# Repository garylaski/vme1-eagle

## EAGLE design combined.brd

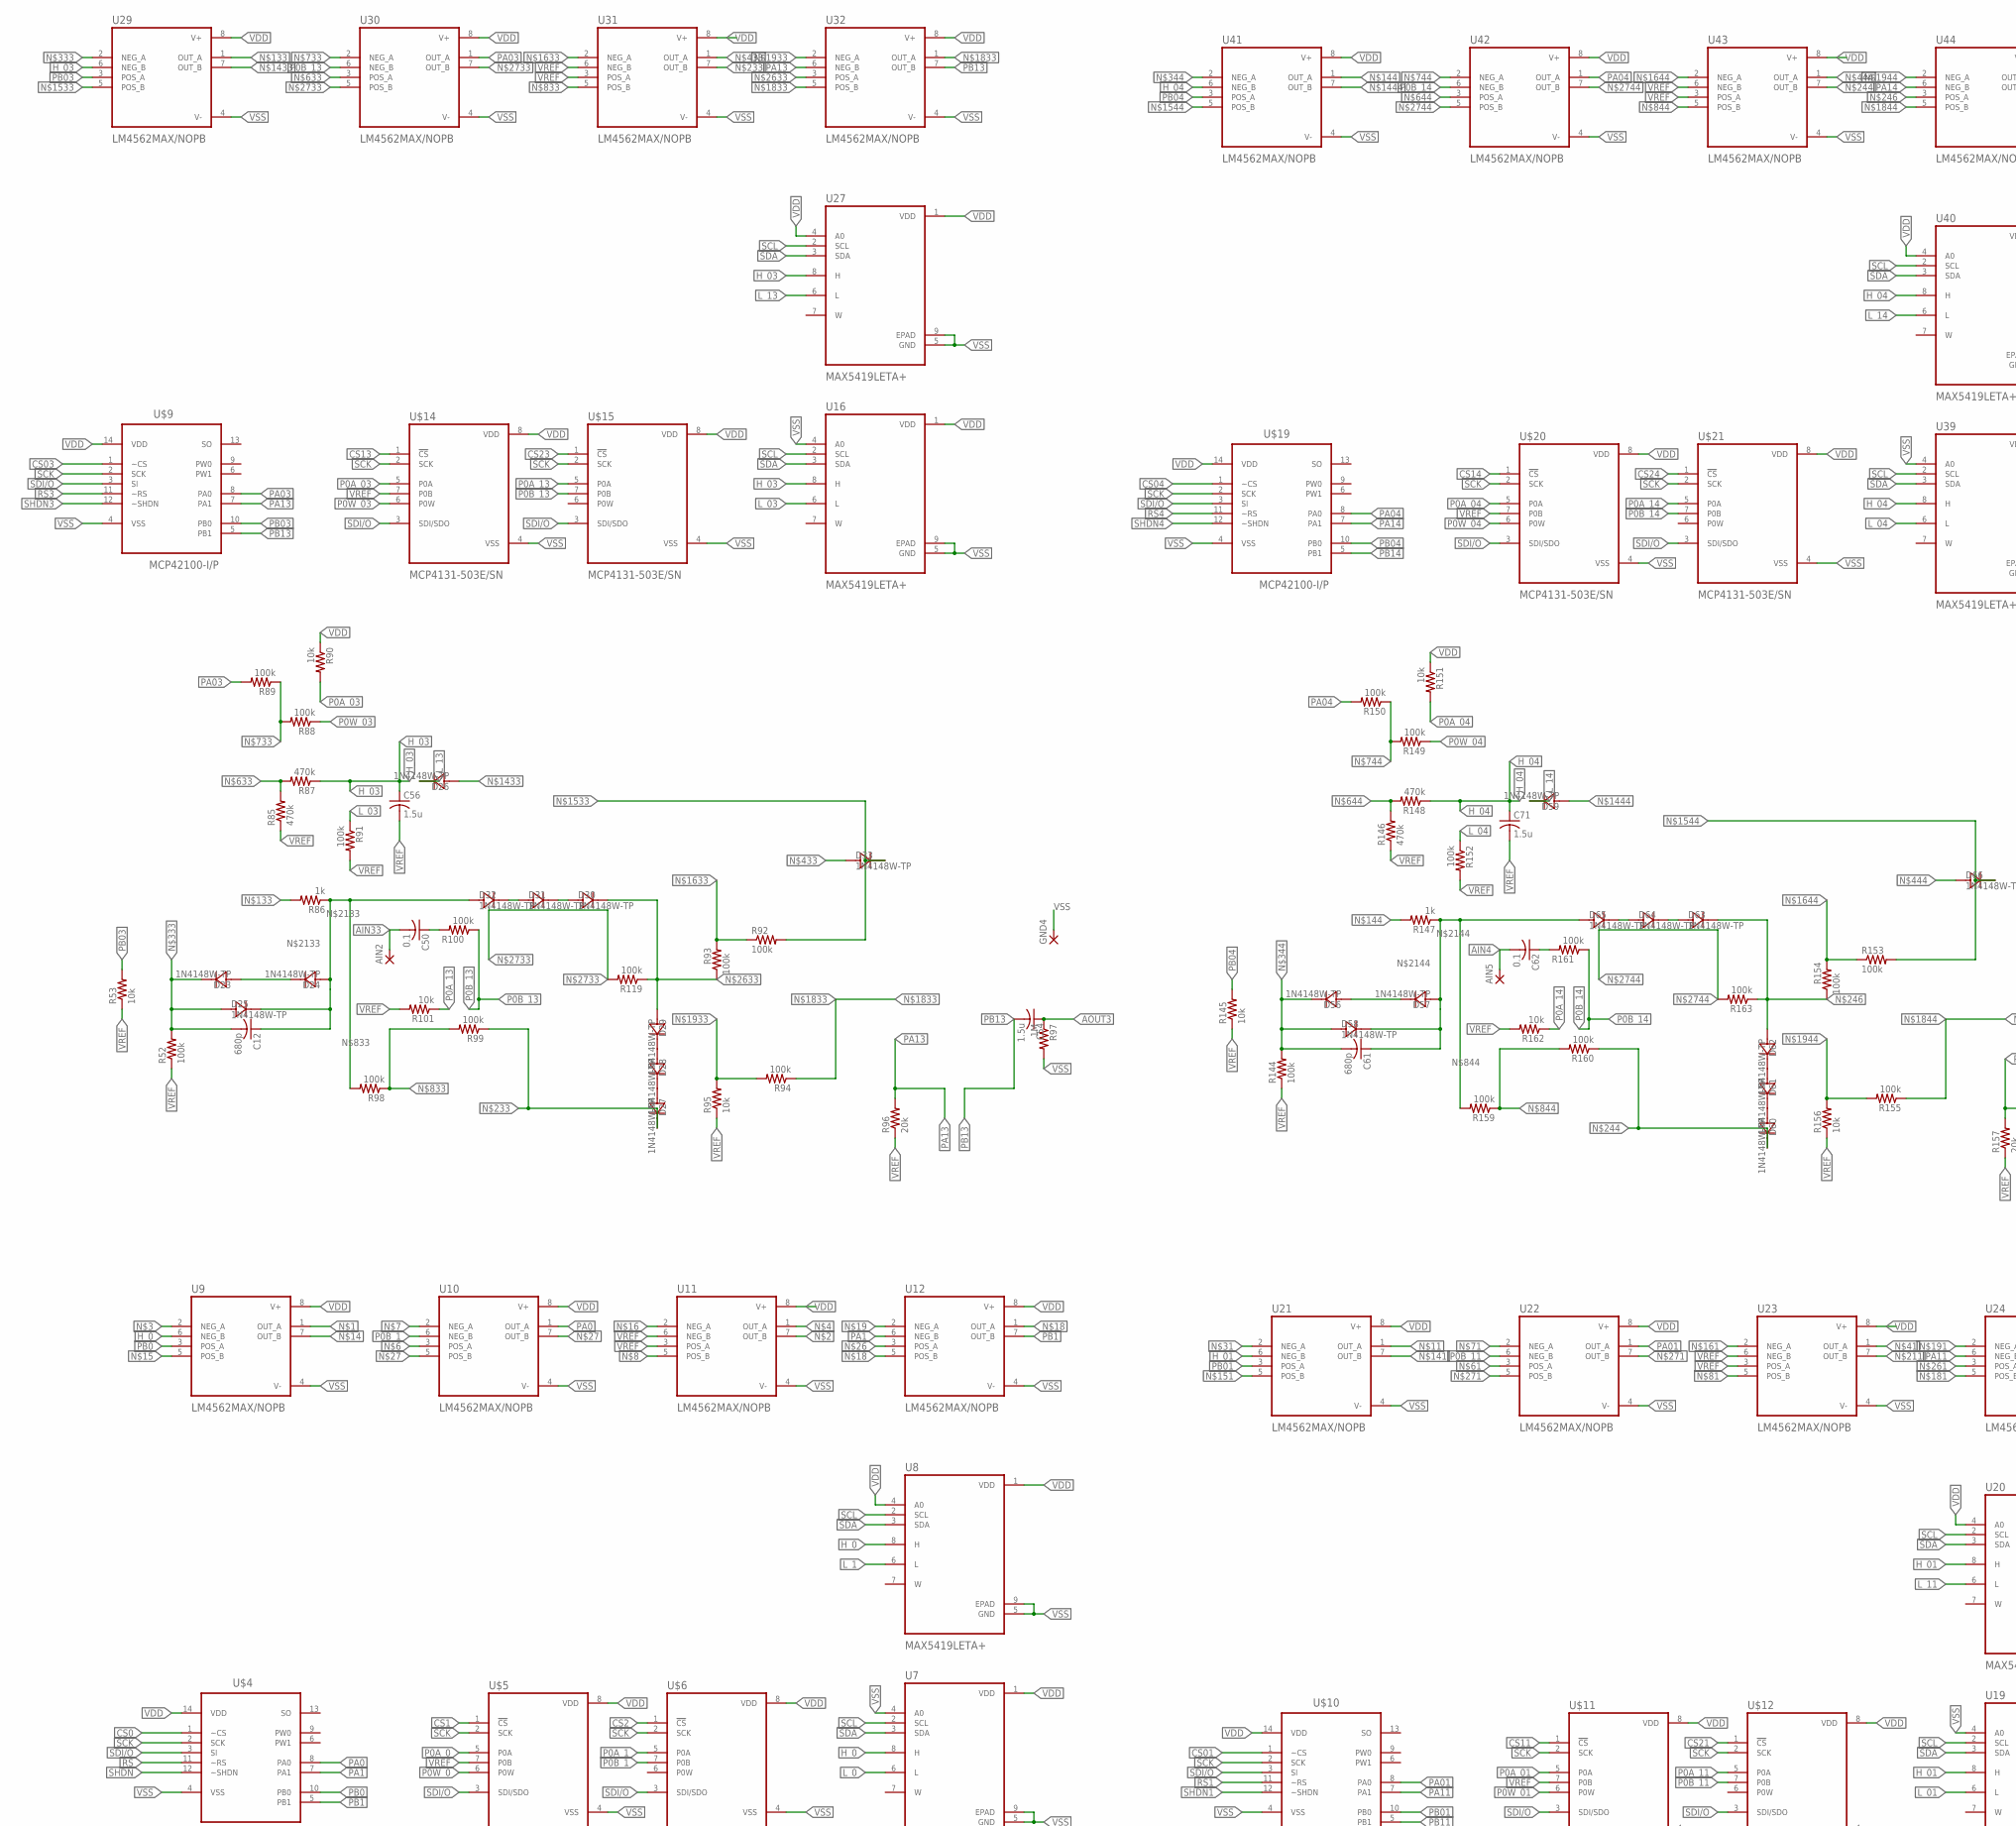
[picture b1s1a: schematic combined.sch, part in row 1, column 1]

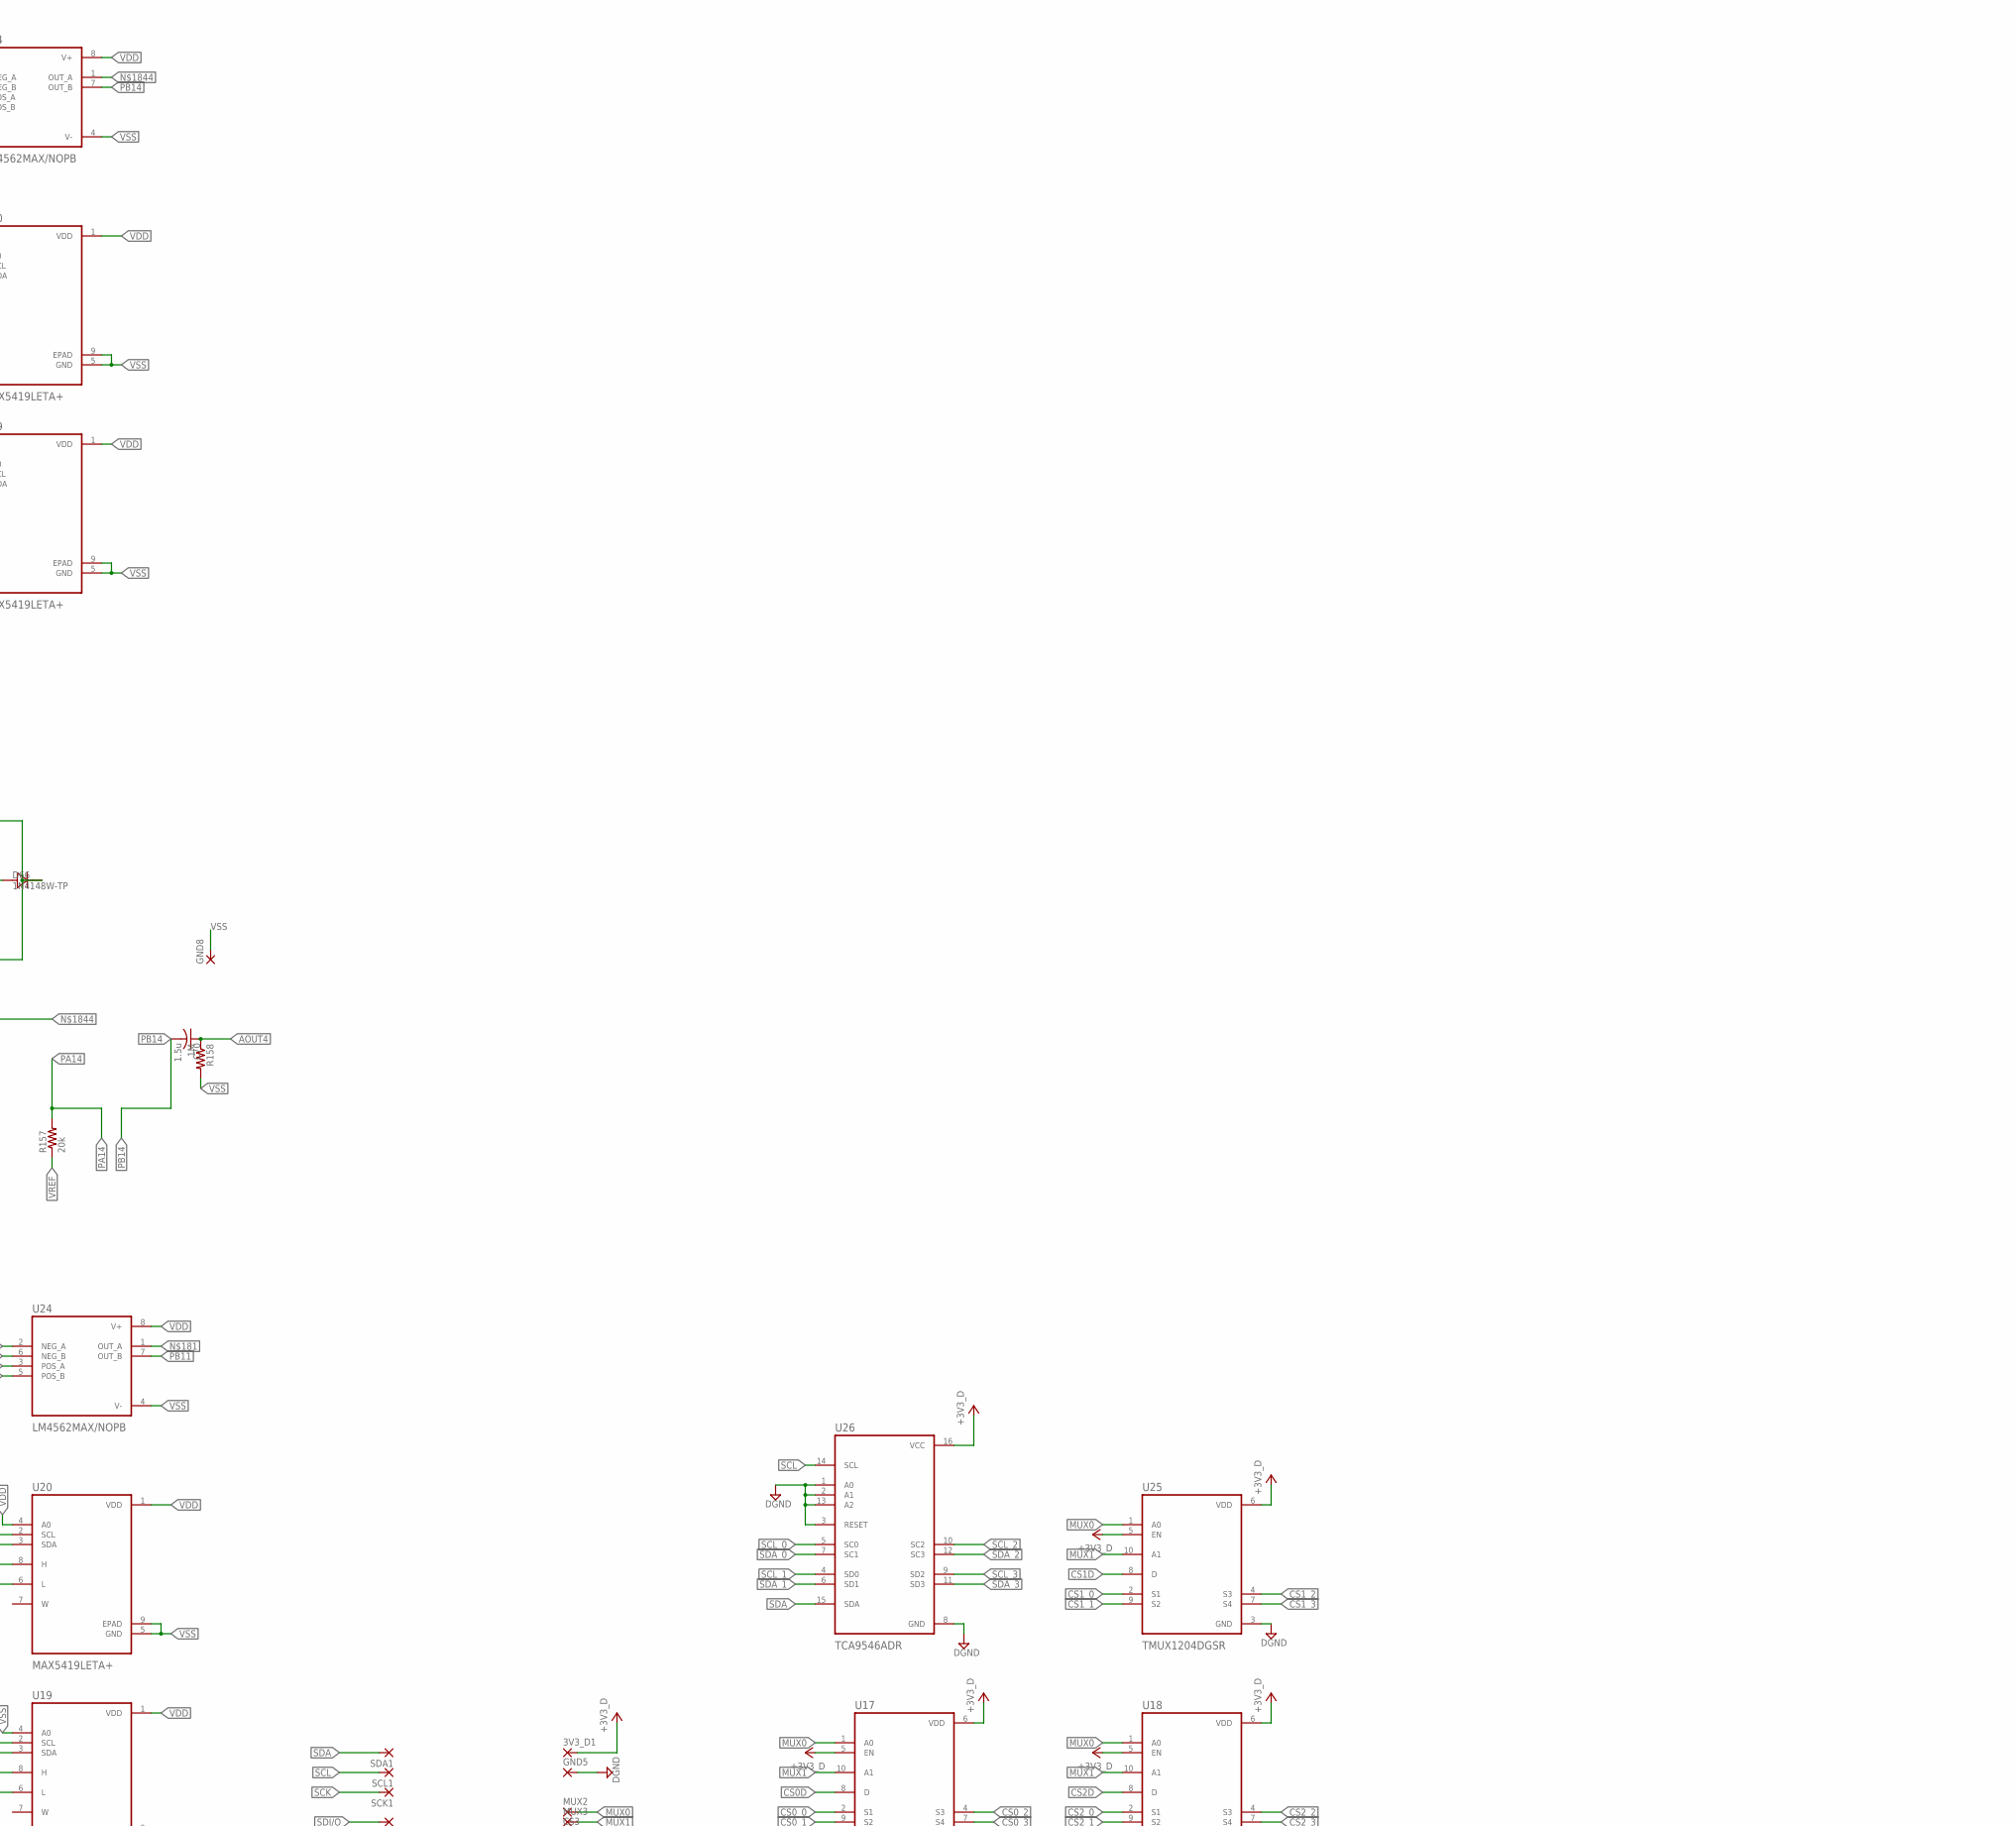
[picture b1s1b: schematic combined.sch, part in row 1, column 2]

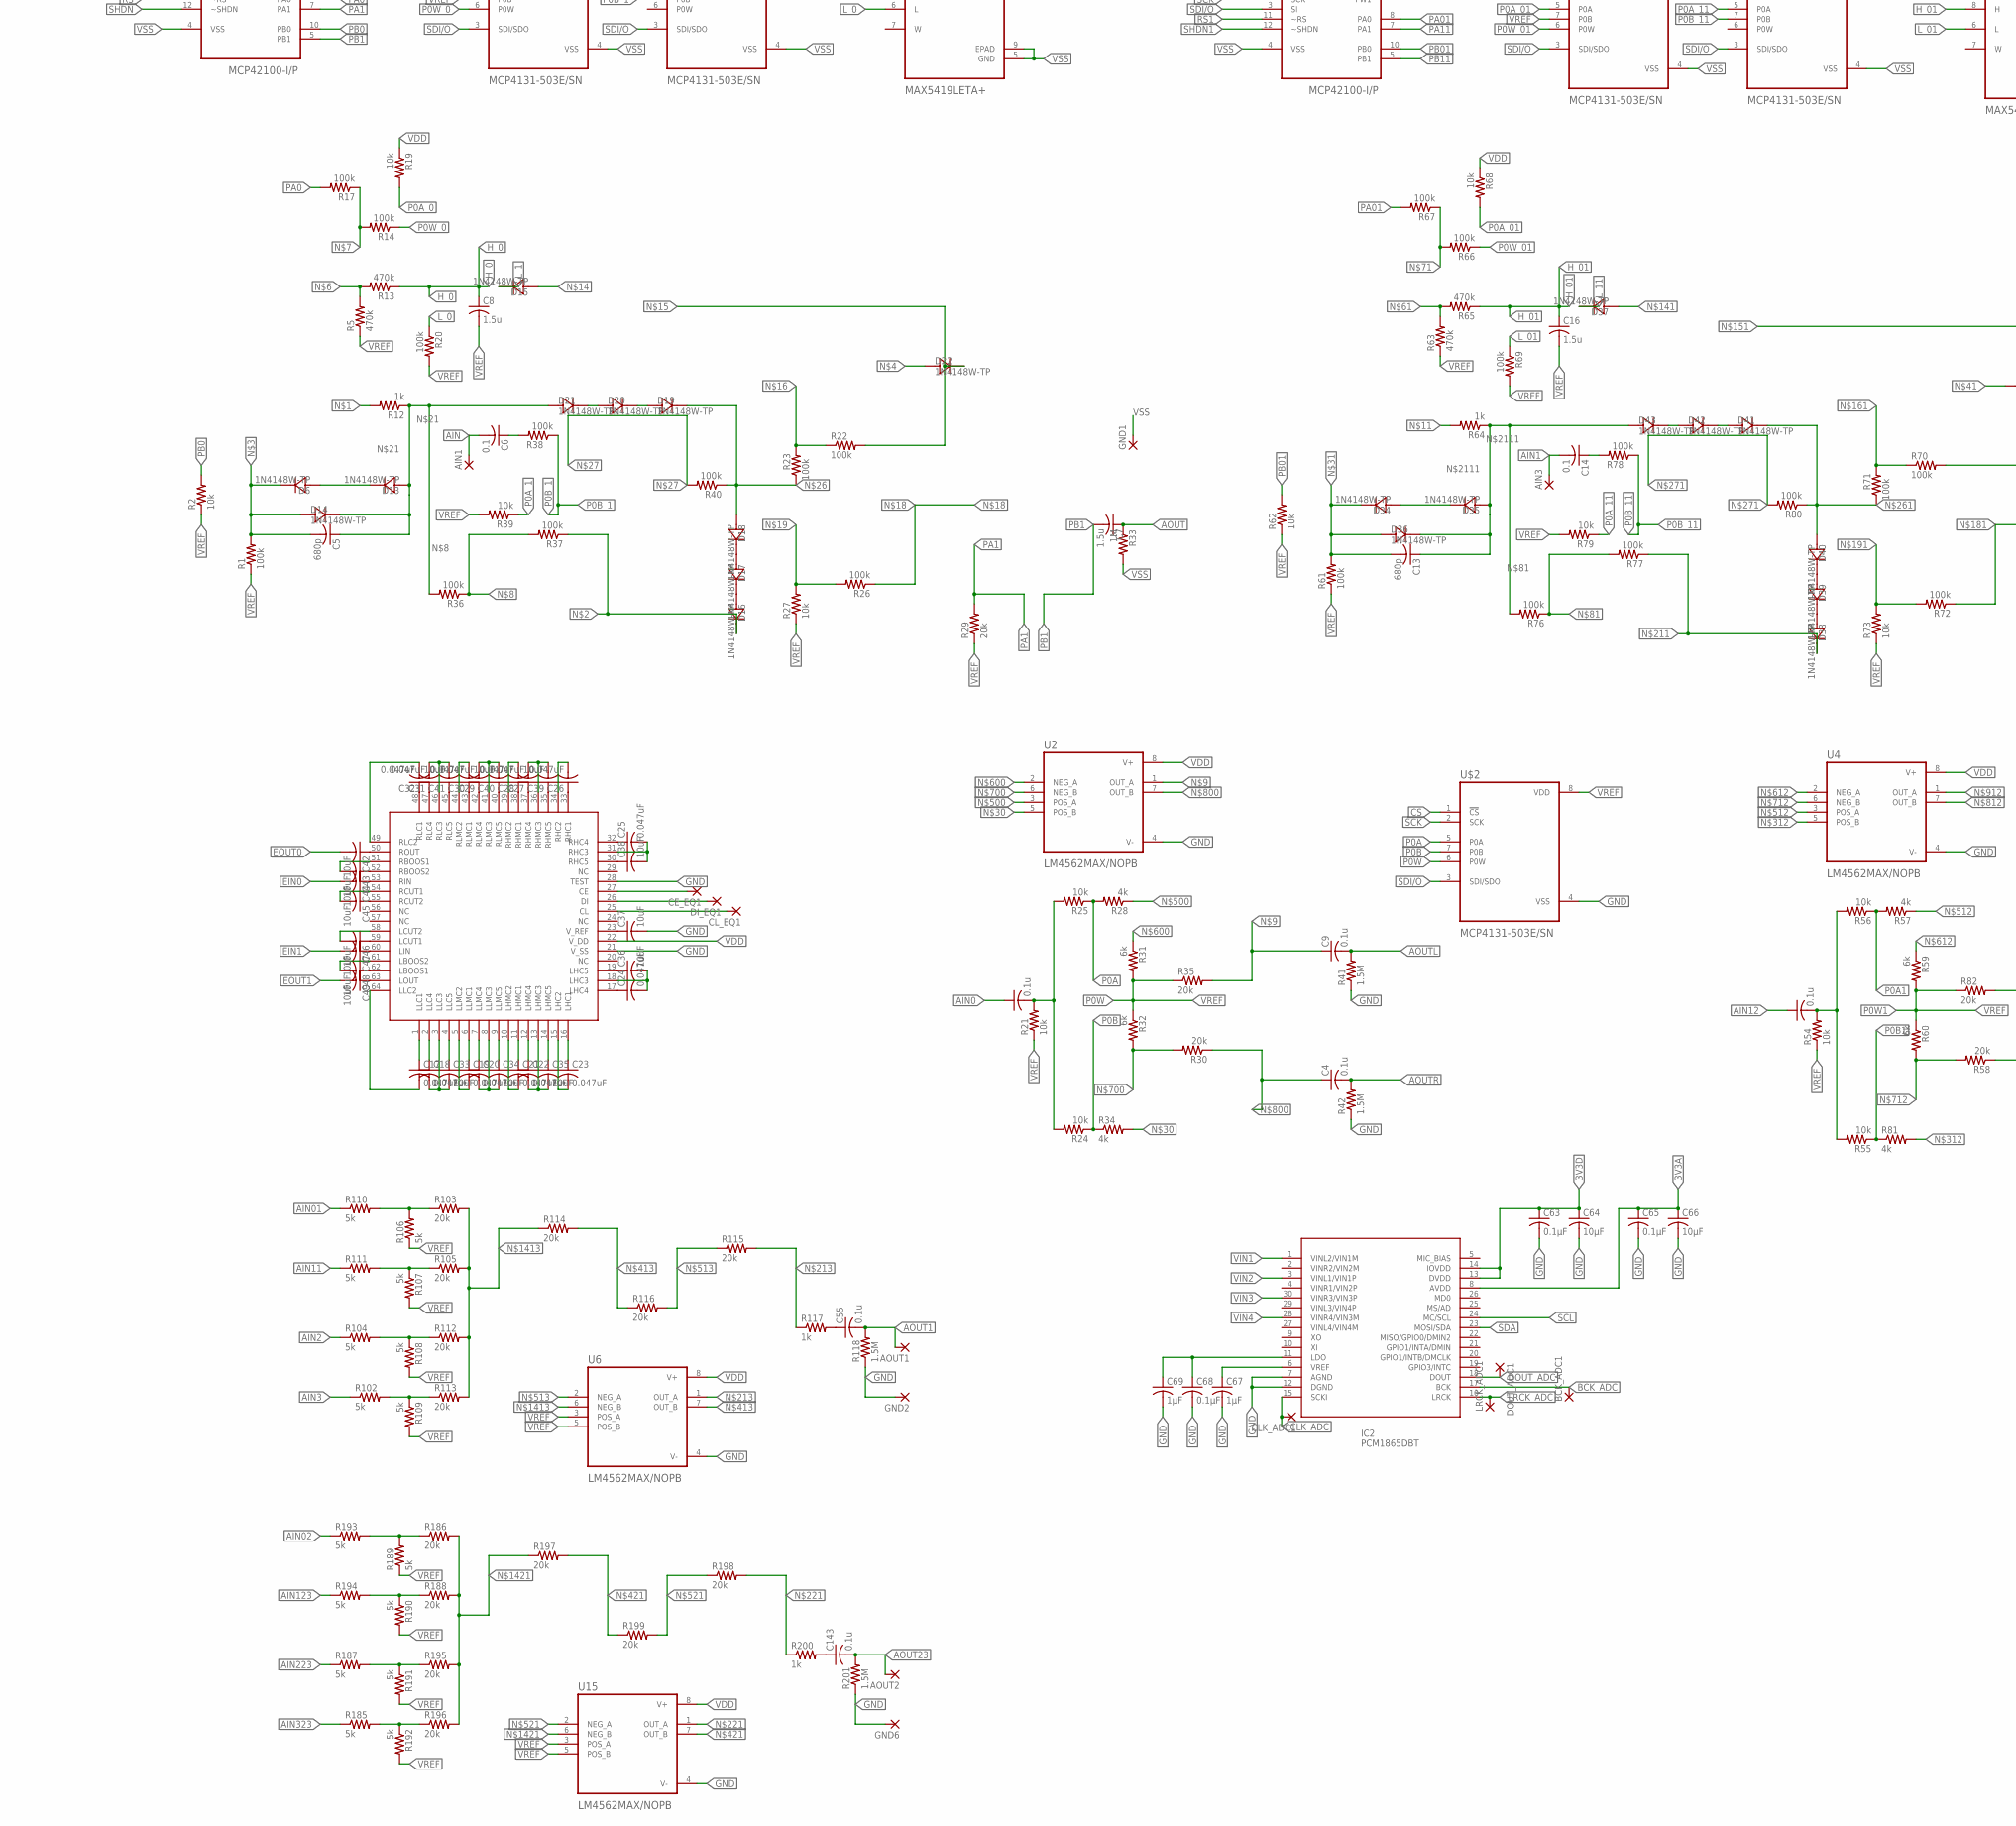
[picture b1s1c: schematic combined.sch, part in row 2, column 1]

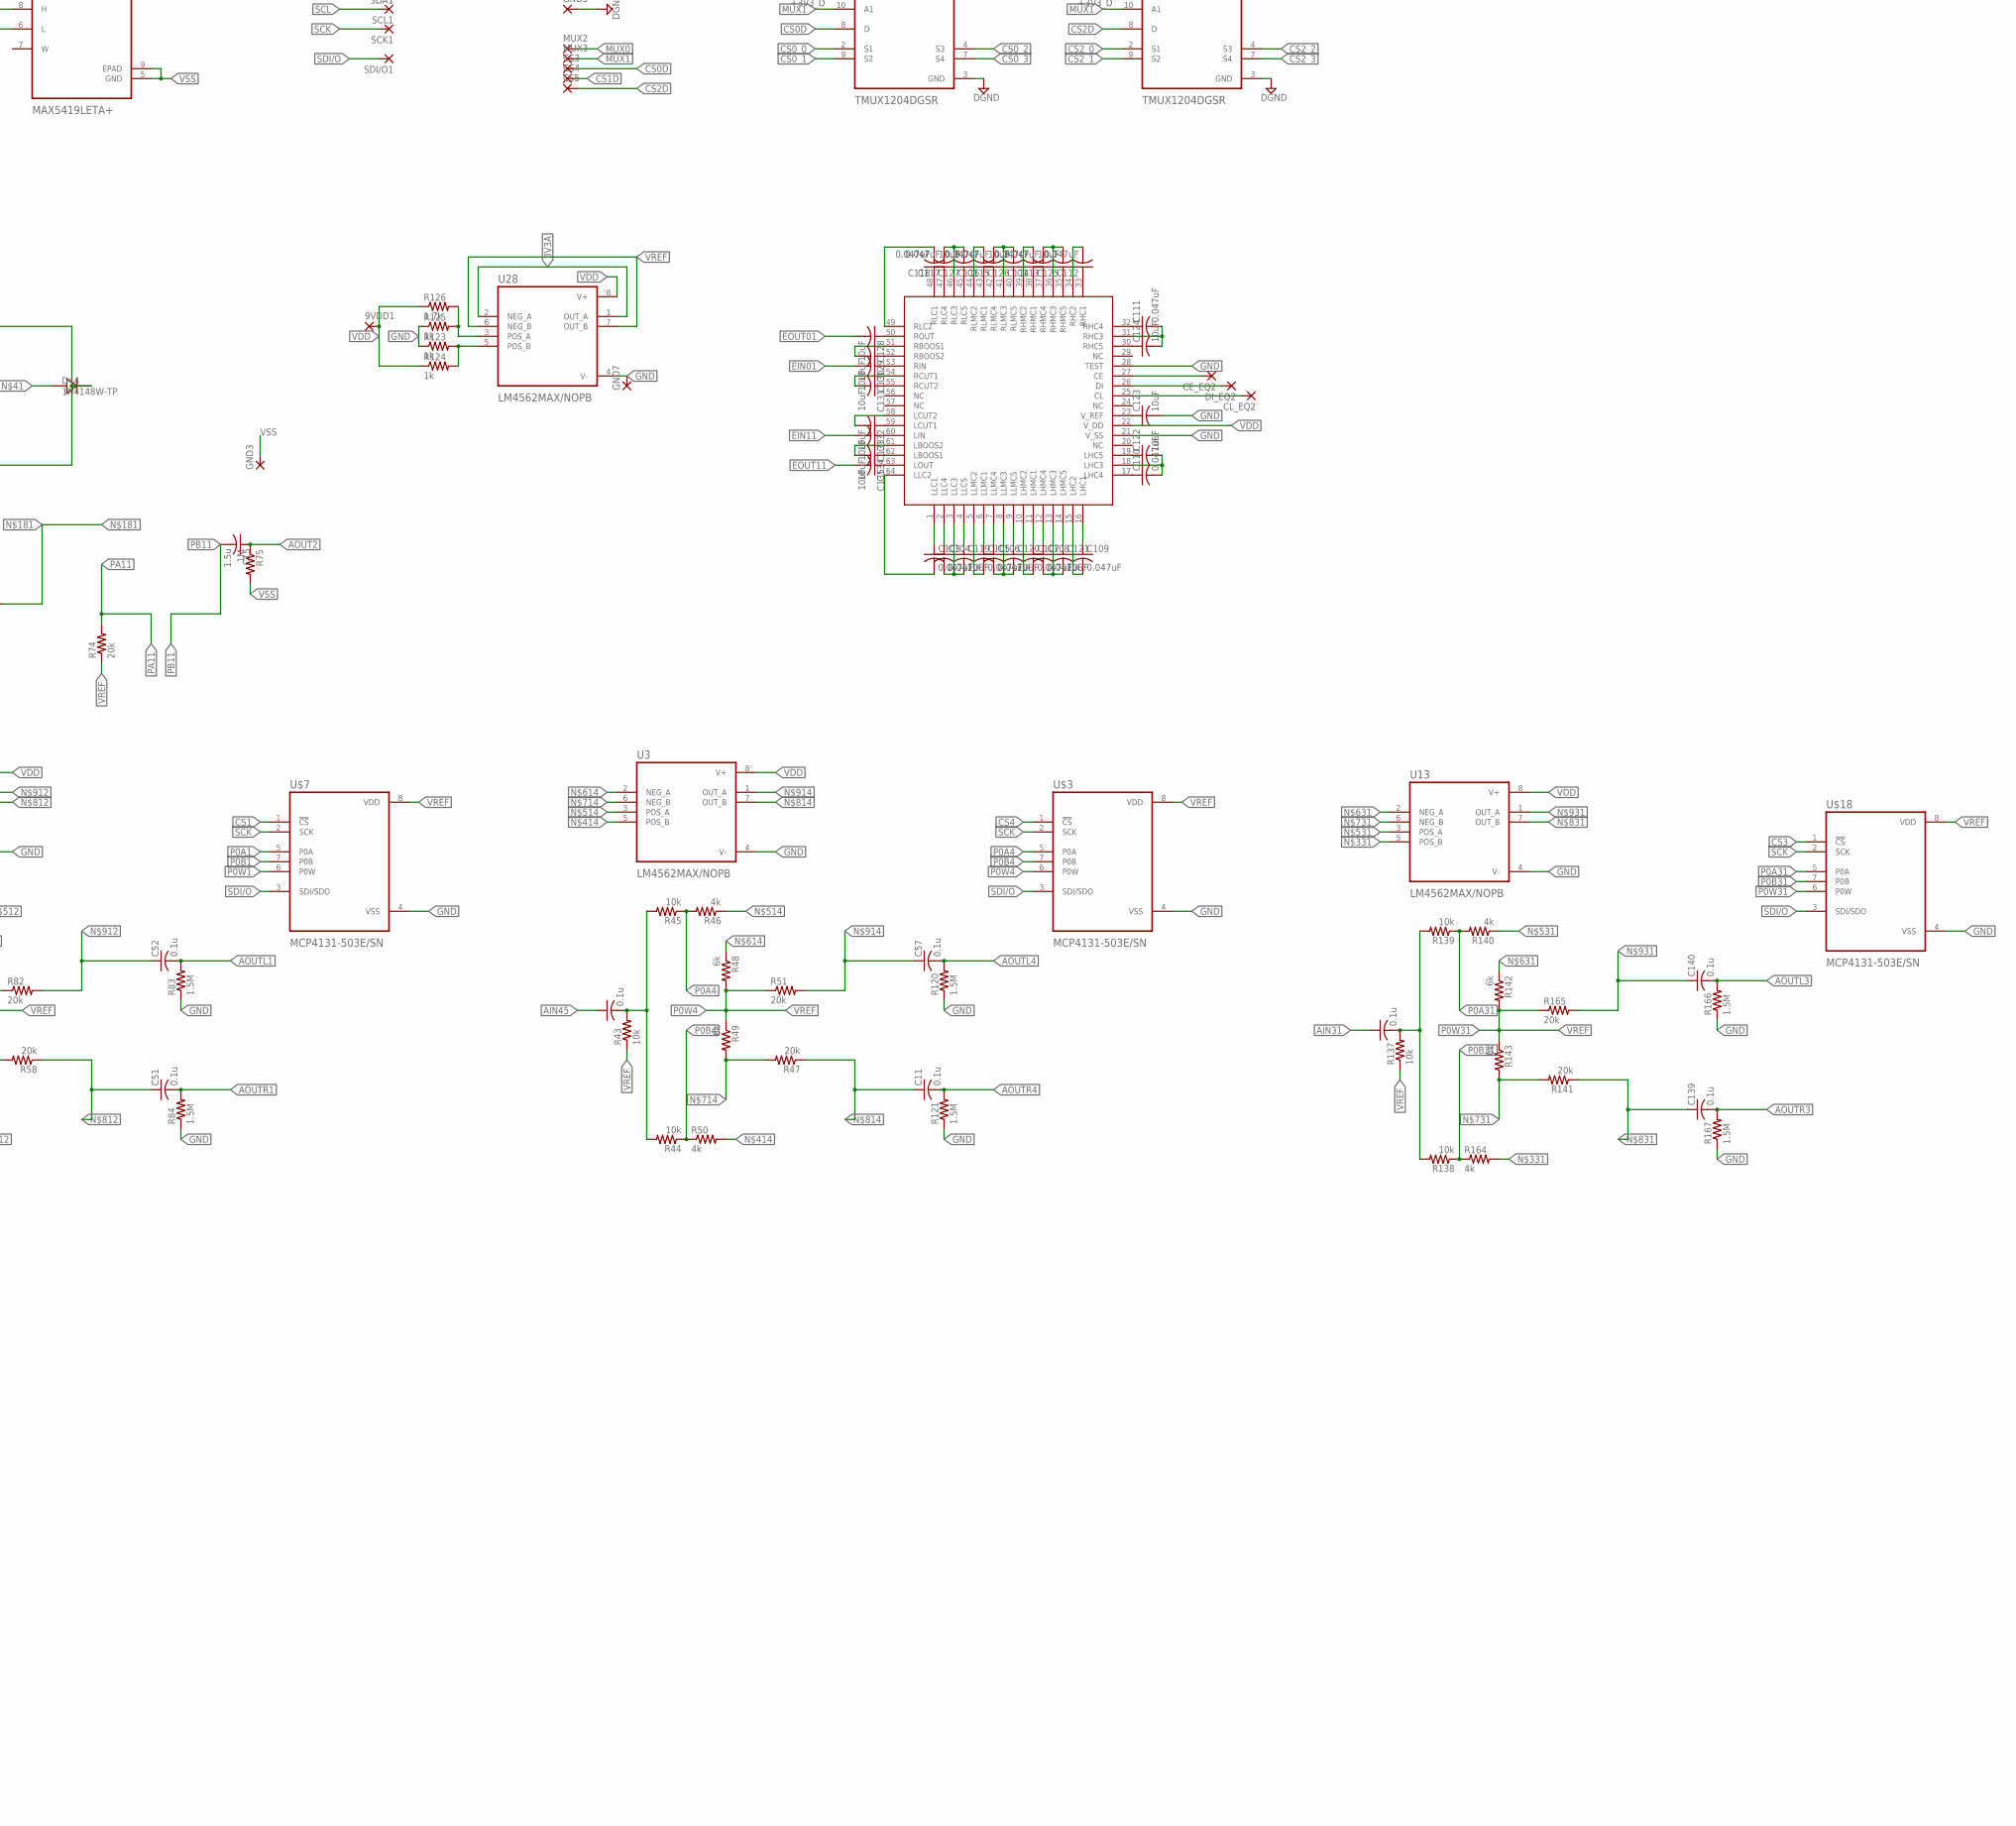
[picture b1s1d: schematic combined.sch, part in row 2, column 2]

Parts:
3V3_D1, 9VDD1: SMD2; SMD1,27-2,54
AIN1, AIN2, AIN3, AIN5: SMD5; SMD2,54-5,08
AOUT1, AOUT2: SMD5; SMD2,54-5,08
BCK_ADC1: SMD2; SMD1,27-2,54
C4, C9, C10, C11, C51, C52, C53, C55, C57, C58, C139, C140, C141, C143: 0.1u; C0402
C5, C12, C13, C61: 680p; C0402
C6, C14, C50, C62: 0.1; C0402
C7, C8, C15, C16, C54, C56, C70, C71: 1.5u; C0402
C17, C18, C19, C20, C21, C22, C23, C24, C25, C26, C27, C28, C29, C30, C31, C32, C103, C104, C105, C106, C107, C108, C109, C110, C111, C112, C113, C114, C115, C116, C117, C118: 0.047uF; C0402
C33, C34, C35, C36, C37, C38, C39, C40, C41, C42, C43, C44, C45, C46, C47, C48, C49, C119, C120, C121, C122, C123, C124, C125, C126, C127, C128, C129, C130, C131, C132, C133, C134, C135: 10uF; C0402
C63, C65, C68: 0.1μF; C0402
C64, C66: 10μF; C0402
C67, C69: 1μF; C0402
CE_EQ1, CE_EQ2: SMD2; SMD1,27-2,54
CLK_ADC1: SMD2; SMD1,27-2,54
CL_EQ1, CL_EQ2: SMD2; SMD1,27-2,54
CS3, CS4, CS5: SMD2; SMD1,27-2,54
D6, D13, D14, D15, D16, D17, D18, D19, D20, D21, D22, D23, D24, D25, D26, D27, D28, D29, D30, D31, D32, D33, D34, D35, D36, D37, D38, D39, D40, D41, D42, D43, D44, D56, D57, D58, D59, D60, D61, D62, D63, D64, D65, D66: 1N4148W-TP; SOD123
DI_EQ1, DI_EQ2: SMD2; SMD1,27-2,54
DOUT_ADC1: SMD2; SMD1,27-2,54
GND1, GND2, GND3, GND4, GND6, GND8: SMD5; SMD2,54-5,08
GND5, GND7: SMD2; SMD1,27-2,54
IC2: PCM1865DBT; TSSOP-30
LRCK_ADC1: SMD2; SMD1,27-2,54
MUX2, MUX3: SMD2; SMD1,27-2,54
R1, R14, R17, R20, R22, R23, R26, R36, R37, R38, R40, R52, R61, R66, R67, R69, R70, R71, R72, R76, R77, R78, R80, R88, R89, R91, R92, R93, R94, R98, R99, R100, R119, R144, R149, R150, R152, R153, R154, R155, R159, R160, R161, R163: 100k; R0402
R2, R19, R21, R24, R25, R27, R39, R43, R44, R45, R53, R54, R55, R56, R62, R68, R73, R79, R90, R95, R101, R137, R138, R139, R145, R151, R156, R162: 10k; R0402
R5, R13, R63, R65, R85, R87, R146, R148: 470k; R0402
R12, R64, R86, R117, R123, R124, R125, R147, R200: 1k; R0402
R28, R34, R46, R50, R57, R81, R140, R164: 4k; R0402
R29, R30, R35, R47, R51, R58, R74, R82, R96, R103, R105, R112, R113, R114, R115, R116, R141, R157, R165, R186, R188, R195, R196, R197, R198, R199: 20k; R0402
R31, R32, R48, R49, R59, R60, R142, R143: 6k; R0402
R33, R75, R97, R158: 1M; R0402
R41, R42, R83, R84, R118, R120, R121, R166, R167, R201: 1.5M; R0402
R102, R104, R106, R107, R108, R109, R110, R111, R185, R187, R189, R190, R191, R192, R193, R194: 5k; R0402
R126: 1.7k; R0402
SCK1: SMD2; SMD1,27-2,54
SCL1: SMD2; SMD1,27-2,54
SDA1: SMD2; SMD1,27-2,54
SDI/O1: SMD2; SMD1,27-2,54
U2, U3, U4, U6, U9, U10, U11, U12, U13, U15, U21, U22, U23, U24, U28, U29, U30, U31, U32, U41, U42, U43, U44: LM4562MAX/NOPB; SOIC127P599X175-8N
U7, U8, U16, U19, U20, U27, U39, U40: MAX5419LETA+; SON65P300X300X80-9N
U17, U18, U25: TMUX1204DGSR; SOP50P490X110-10N
U26: TCA9546ADR; SOIC127P600X175-16N
U$2, U$3, U$5, U$6, U$7, U$11, U$12, U$14, U$15, U$18, U$20, U$21: MCP4131-503E/SN; SOIC127P599X175-8N
U$4, U$9, U$10, U$19: MCP42100-I/P; DIP254P762X432-14
U$13, U$16: LC75281E; QFP80P1720X1720X270-64N

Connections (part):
3V3A: C65.1, C66.1, IC2.8 (AVDD), U28.1 (OUT_A), U28.2 (NEG_A)
3V3D: C63.1, C64.1, IC2.13 (DVDD), IC2.14 (IOVDD)
+3V3: 3V3_D1.1, U17.5 (EN), U17.6 (VDD), U18.5 (EN), U18.6 (VDD), U25.5 (EN), U25.6 (VDD), U26.16 (VCC)
AIN: AIN1.1, C6.2
AIN0: C10.1
AIN1: AIN3.1, C14.2
AIN01: R110.1
AIN2: R104.1
AIN02: R193.1
AIN3: R102.1
AIN4: AIN5.1, C62.2
AIN11: R111.1
AIN12: C53.1
AIN31: C141.1
AIN33: AIN2.1, C50.2
AIN45: C58.1
AIN123: R194.1
AIN223: R187.1
AIN323: R185.1
AOUT: C7.1, R33.1
AOUT1: AOUT1.1, C55.2, R118.2
AOUT2: C15.1, R75.1
AOUT3: C54.1, R97.1
AOUT4: C70.1, R158.1
AOUT23: AOUT2.1, C143.2, R201.2
AOUTL: C9.2, R41.2
AOUTL1: C52.2, R83.2
AOUTL3: C140.2, R166.2
AOUTL4: C57.2, R120.2
AOUTR: C4.2, R42.2
AOUTR1: C51.2, R84.2
AOUTR3: C139.2, R167.2
AOUTR4: C11.2, R121.2
BCK_ADC: BCK_ADC1.1, IC2.17 (BCK)
CLK_ADC: CLK_ADC1.1, IC2.15 (SCKI)
CS: U$2.1 (!CS)
CS0: U$4.1 (~CS)
CS0D: CS3.1, U17.8 (D)
CS0_0: U17.2 (S1)
CS0_1: U17.9 (S2)
CS0_2: U17.4 (S3)
CS0_3: U17.7 (S4)
CS1: U$5.1 (!CS), U$7.1 (!CS)
CS01: U$10.1 (~CS)
CS1D: CS4.1, U25.8 (D)
CS1_0: U25.2 (S1)
CS1_1: U25.9 (S2)
CS1_2: U25.4 (S3)
CS1_3: U25.7 (S4)
CS2: U$6.1 (!CS)
CS2D: CS5.1, U18.8 (D)
CS2_0: U18.2 (S1)
CS2_1: U18.9 (S2)
CS2_2: U18.4 (S3)
CS2_3: U18.7 (S4)
CS03: U$9.1 (~CS)
CS3: U$18.1 (!CS)
CS04: U$19.1 (~CS)
CS4: U$3.1 (!CS)
CS11: U$11.1 (!CS)
CS13: U$14.1 (!CS)
CS14: U$20.1 (!CS)
CS21: U$12.1 (!CS)
CS23: U$15.1 (!CS)
CS24: U$21.1 (!CS)
DGND: GND5.1, U17.3 (GND), U18.3 (GND), U25.3 (GND), U26.1 (A0), U26.2 (A1), U26.3 (RESET), U26.8 (GND), U26.13 (A2)
DOUT_ADC: DOUT_ADC1.1, IC2.18 (DOUT)
EIN0: C44.2
EIN1: C47.2
EIN01: C130.2
EIN11: C133.2
EOUT0: C42.2
EOUT1: C49.2
EOUT01: C128.2
EOUT11: C135.2
EQ1_CE1: CE_EQ1.1, U$13.27 (CE)
EQ1_CE2: CE_EQ2.1, U$16.27 (CE)
EQ1_CL1: CL_EQ1.1, U$13.25 (CL)
EQ1_CL2: CL_EQ2.1, U$16.25 (CL)
EQ1_DI1: DI_EQ1.1, U$13.26 (DI)
EQ1_DI2: DI_EQ2.1, U$16.26 (DI)
GND: C37.2, C63.2, C64.2, C65.2, C66.2, C67.2, C68.2, C69.2, C123.2, GND2.1, GND6.1, GND7.1, IC2.7 (AGND), IC2.12 (DGND), R41.1, R42.1, R83.1, R84.1, R118.1, R120.1, R121.1, R123.1, R125.1, R166.1, R167.1, R201.1, U2.4 (V-), U3.4 (V-), U4.4 (V-), U6.4 (V-), U13.4 (V-), U15.4 (V-), U28.4 (V-), U$2.4 (VSS), U$3.4 (VSS), U$7.4 (VSS), U$13.21 (V_SS), U$13.28 (TEST), U$16.21 (V_SS), U$16.28 (TEST), U$18.4 (VSS)
H_0: C8.1, R13.1, U7.8 (H), U8.8 (H), U9.6 (NEG_B)
H_01: C16.1, R65.1, U19.8 (H), U20.8 (H), U21.6 (NEG_B)
H_03: C56.1, R87.1, U16.8 (H), U27.8 (H), U29.6 (NEG_B)
H_04: C71.1, R148.1, U39.8 (H), U40.8 (H), U41.6 (NEG_B)
LRCK_ADC: IC2.16 (LRCK), LRCK_ADC1.1
L_0: R20.1, U7.6 (L)
L_1: D15.C, U8.6 (L)
L_01: R69.1, U19.6 (L)
L_03: R91.1, U16.6 (L)
L_04: R152.1, U39.6 (L)
L_11: D37.C, U20.6 (L)
L_13: D26.C, U27.6 (L)
L_14: D59.C, U40.6 (L)
MUX0: MUX2.1, U17.1 (A0), U18.1 (A0), U25.1 (A0)
MUX1: MUX3.1, U17.10 (A1), U18.10 (A1), U25.10 (A1)
unnamed: D6.A, D13.C, R12.2, U9.1 (OUT_A)
unnamed: D16.C, D17.A, D18.C, R37.1, U11.7 (OUT_B)
unnamed: C5.2, D6.C, D14.A, D16.A, D17.C, R1.2, U9.2 (NEG_A)
unnamed: C6.1, D22.A, R38.2, U11.1 (OUT_A)
unnamed: D20.A, D21.C
unnamed: D19.A, D20.C, R5.2, R13.2, U10.3 (POS_A)
unnamed: R14.2, R17.1, U10.2 (NEG_A)
unnamed: R36.1, R37.2, U11.5 (POS_B)
unnamed: C9.1, R35.2, U2.1 (OUT_A)
unnamed: C10.2, R21.2, R24.2, R25.2
unnamed: R64.2, U21.1 (OUT_A)
unnamed: D34.A, D35.C
unnamed: D15.A, U9.7 (OUT_B)
unnamed: D22.C, R22.2, U9.5 (POS_B)
unnamed: R22.1, R23.2, U11.2 (NEG_A)
unnamed: D42.A, D43.C
unnamed: R26.1, U12.1 (OUT_A), U12.5 (POS_B)
unnamed: R26.2, R27.2, U12.2 (NEG_A)
unnamed: C58.2, R43.2, R44.2, R45.2
unnamed: C5.1, D13.A, D14.C, D21.A, R12.1, R36.2
unnamed: C19.1, U$13.6 (LLMC1)
unnamed: C20.1, U$13.7 (LLMC4)
unnamed: D18.A, D19.C, R23.1, R40.1, U12.3 (POS_A)
unnamed: R40.2, U10.5 (POS_B), U10.7 (OUT_B)
unnamed: C23.1, U$13.16 (LHC1)
unnamed: C24.1, U$13.17 (LHC4)
unnamed: R34.2, U2.5 (POS_B)
unnamed: C13.2, D34.C, D36.A, R61.2, U21.2 (NEG_A)
unnamed: C25.1, U$13.32 (RHC4)
unnamed: C26.1, U$13.33 (RHC1)
unnamed: C27.1, U$13.37 (RHMC4)
unnamed: C28.1, U$13.38 (RHMC1)
unnamed: C29.1, U$13.42 (RLMC4)
unnamed: C30.1, U$13.43 (RLMC1)
unnamed: C31.1, U$13.47 (RLC4)
unnamed: C32.1, U$13.48 (RLC1)
unnamed: D44.A, U23.1 (OUT_A)
unnamed: C18.2, C33.2, U$13.3 (LLC3)
unnamed: C33.1, U$13.4 (LLC5)
unnamed: C34.1, U$13.9 (LLMC5)
unnamed: C35.1, U$13.14 (LHMC5)
unnamed: C36.1, U$13.19 (LHC5)
unnamed: C37.1, U$13.23 (V_REF)
unnamed: C38.1, U$13.30 (RHC5)
unnamed: C39.1, U$13.35 (RHMC5)
unnamed: C40.1, U$13.40 (RLMC5)
unnamed: C41.1, U$13.45 (RLC5)
unnamed: C42.1, U$13.50 (ROUT)
unnamed: C43.1, U$13.52 (RBOOS2)
unnamed: C44.1, U$13.53 (RIN)
unnamed: C45.1, U$13.55 (RCUT2)
unnamed: C46.1, U$13.59 (LCUT1)
unnamed: C47.1, U$13.60 (LIN)
unnamed: C48.1, U$13.62 (LBOOS1)
unnamed: C49.1, U$13.63 (LOUT)
unnamed: C19.2, U$13.5 (LLMC2)
unnamed: R63.2, R65.2, U22.3 (POS_A)
unnamed: C21.2, U$13.10 (LHMC2)
unnamed: C22.2, C35.2, U$13.13 (LHMC3)
unnamed: C23.2, U$13.15 (LHC2)
unnamed: C24.2, C36.2, U$13.18 (LHC3)
unnamed: C25.2, C38.2, U$13.31 (RHC3)
unnamed: C26.2, U$13.34 (RHC2)
unnamed: C27.2, C39.2, U$13.36 (RHMC3)
unnamed: C28.2, U$13.39 (RHMC2)
unnamed: C29.2, C40.2, U$13.41 (RLMC3)
unnamed: R66.2, R67.1, U22.2 (NEG_A)
unnamed: C31.2, C41.2, U$13.46 (RLC3)
unnamed: C32.2, U$13.49 (RLC2)
unnamed: C43.2, U$13.51 (RBOOS1)
unnamed: C45.2, U$13.54 (RCUT1)
unnamed: C46.2, U$13.58 (LCUT2)
unnamed: C48.2, U$13.61 (LBOOS2)
unnamed: C18.1, U$13.2 (LLC4)
unnamed: C55.1, R117.2
unnamed: R76.1, R77.2, U23.5 (POS_B)
unnamed: R103.1, R106.2, R110.2
unnamed: R102.2, R109.1, R113.1
unnamed: R104.2, R108.1, R112.1
unnamed: R105.1, R107.1, R111.2
unnamed: D23.A, D24.C
unnamed: D28.A, D29.C
unnamed: C67.1, IC2.6 (VREF)
unnamed: C68.1, C69.1, IC2.11 (LDO)
unnamed: D27.A, D28.C
unnamed: C50.1, R100.2
unnamed: R125.2, R126.2, U28.3 (POS_A)
unnamed: R123.2, R124.2, U28.5 (POS_B)
unnamed: D31.A, D32.C
unnamed: D30.A, D31.C
unnamed: C103.1, U$16.1 (LLC1)
unnamed: C105.1, U$16.6 (LLMC1)
unnamed: C106.1, U$16.7 (LLMC4)
unnamed: D56.A, D57.C
unnamed: D61.A, D62.C
unnamed: D60.A, D61.C
unnamed: C62.1, R161.2
unnamed: D64.A, D65.C
unnamed: D63.A, D64.C
unnamed: C107.1, U$16.11 (LHMC1)
unnamed: C108.1, U$16.12 (LHMC4)
unnamed: C109.1, U$16.16 (LHC1)
unnamed: C110.1, U$16.17 (LHC4)
unnamed: C111.1, U$16.32 (RHC4)
unnamed: C112.1, U$16.33 (RHC1)
unnamed: C113.1, U$16.37 (RHMC4)
unnamed: C114.1, U$16.38 (RHMC1)
unnamed: C115.1, U$16.42 (RLMC4)
unnamed: C116.1, U$16.43 (RLMC1)
unnamed: C117.1, U$16.47 (RLC4)
unnamed: C118.1, U$16.48 (RLC1)
unnamed: C103.2, U$16.64 (LLC2)
unnamed: C104.2, C119.2, U$16.3 (LLC3)
unnamed: C119.1, U$16.4 (LLC5)
unnamed: C120.1, U$16.9 (LLMC5)
unnamed: C121.1, U$16.14 (LHMC5)
unnamed: C122.1, U$16.19 (LHC5)
unnamed: R86.2, U29.1 (OUT_A)
unnamed: C123.1, U$16.23 (V_REF)
unnamed: C124.1, U$16.30 (RHC5)
unnamed: C125.1, U$16.35 (RHMC5)
unnamed: C126.1, U$16.40 (RLMC5)
unnamed: C127.1, U$16.45 (RLC5)
unnamed: C128.1, U$16.50 (ROUT)
unnamed: D37.A, U21.7 (OUT_B)
unnamed: D39.A, D40.C
unnamed: C129.1, U$16.52 (RBOOS2)
unnamed: R147.2, U41.1 (OUT_A)
unnamed: C130.1, U$16.53 (RIN)
unnamed: C131.1, U$16.55 (RCUT2)
unnamed: C132.1, U$16.59 (LCUT1)
unnamed: C133.1, U$16.60 (LIN)
unnamed: C134.1, U$16.62 (LBOOS1)
unnamed: C135.1, U$16.63 (LOUT)
unnamed: D44.C, R70.2, U21.5 (POS_B)
unnamed: D38.A, D39.C
unnamed: C105.2, U$16.5 (LLMC2)
unnamed: C106.2, C120.2, U$16.8 (LLMC3)
unnamed: C107.2, U$16.10 (LHMC2)
unnamed: C108.2, C121.2, U$16.13 (LHMC3)
unnamed: C109.2, U$16.15 (LHC2)
unnamed: C110.2, C122.2, U$16.18 (LHC3)
unnamed: C111.2, C124.2, U$16.31 (RHC3)
unnamed: C112.2, U$16.34 (RHC2)
unnamed: R70.1, R71.2, U23.2 (NEG_A)
unnamed: C14.1, R78.2
unnamed: C113.2, C125.2, U$16.36 (RHMC3)
unnamed: C114.2, U$16.39 (RHMC2)
unnamed: C115.2, C126.2, U$16.41 (RLMC3)
unnamed: C116.2, U$16.44 (RLMC2)
unnamed: C117.2, C127.2, U$16.46 (RLC3)
unnamed: C118.2, U$16.49 (RLC2)
unnamed: C129.2, U$16.51 (RBOOS1)
unnamed: C131.2, U$16.54 (RCUT1)
unnamed: C132.2, U$16.58 (LCUT2)
unnamed: C134.2, U$16.61 (LBOOS2)
unnamed: C104.1, U$16.2 (LLC4)
unnamed: C141.2, R137.2, R138.2, R139.2
unnamed: R72.1, U24.1 (OUT_A), U24.5 (POS_B)
unnamed: D41.A, D42.C
unnamed: R72.2, R73.2, U24.2 (NEG_A)
unnamed: D38.C, R77.1, U23.7 (OUT_B)
unnamed: R115.2, R117.1, U6.1 (OUT_A)
unnamed: R198.2, R200.1, U15.1 (OUT_A)
unnamed: C143.1, R200.2
unnamed: R186.1, R189.2, R193.2
unnamed: R185.2, R192.1, R196.1
unnamed: R187.2, R191.1, R195.1
unnamed: R188.1, R190.1, R194.2
unnamed: D27.C, R99.1, U31.7 (OUT_B)
unnamed: D60.C, R160.1, U43.7 (OUT_B)
unnamed: D62.A, D63.C, R154.1, R163.1, U44.3 (POS_A)
unnamed: D40.A, D41.C, R71.1, R80.1, U24.3 (POS_A)
unnamed: R80.2, U22.5 (POS_B), U22.7 (OUT_B)
unnamed: R81.2, U4.5 (POS_B)
unnamed: R164.2, U13.5 (POS_B)
unnamed: C12.2, D23.C, D25.A, R52.2, U29.2 (NEG_A)
unnamed: C61.2, D56.C, D58.A, R144.2, U41.2 (NEG_A)
unnamed: C17.2, U$13.64 (LLC2)
unnamed: R114.2, R116.1, U6.7 (OUT_B)
unnamed: R50.2, U3.5 (POS_B)
unnamed: R197.2, R199.1, U15.7 (OUT_B)
unnamed: D33.A, U31.1 (OUT_A)
unnamed: D66.A, U43.1 (OUT_A)
unnamed: R28.1, U2.3 (POS_A)
unnamed: R57.1, U4.3 (POS_A)
unnamed: R115.1, R116.2, U6.2 (NEG_A)
unnamed: R46.1, U3.3 (POS_A)
unnamed: R198.1, R199.2, U15.2 (NEG_A)
unnamed: R140.1, U13.3 (POS_A)
unnamed: R31.1, U2.2 (NEG_A)
unnamed: C20.2, C34.2, U$13.8 (LLMC3)
unnamed: R59.1, U4.2 (NEG_A)
unnamed: R48.1, U3.2 (NEG_A)
unnamed: R142.1, U13.2 (NEG_A)
unnamed: R85.2, R87.2, U30.3 (POS_A)
unnamed: R146.2, R148.2, U42.3 (POS_A)
unnamed: R30.2, R32.2, U2.6 (NEG_B)
unnamed: C30.2, U$13.44 (RLMC2)
unnamed: R58.2, R60.2, U4.6 (NEG_B)
unnamed: R47.2, R49.2, U3.6 (NEG_B)
unnamed: R141.2, R143.2, U13.6 (NEG_B)
unnamed: R88.2, R89.1, U30.2 (NEG_A)
unnamed: R149.2, R150.1, U42.2 (NEG_A)
unnamed: C4.1, R30.1, U2.7 (OUT_B)
unnamed: C51.1, R58.1, U4.7 (OUT_B)
unnamed: C11.1, R47.1, U3.7 (OUT_B)
unnamed: C139.1, R141.1, U13.7 (OUT_B)
unnamed: R98.1, R99.2, U31.5 (POS_B)
unnamed: R159.1, R160.2, U43.5 (POS_B)
unnamed: C52.1, R82.2, U4.1 (OUT_A)
unnamed: C57.1, R51.2, U3.1 (OUT_A)
unnamed: C140.1, R165.2, U13.1 (OUT_A)
unnamed: R103.2, R105.2, R112.2, R113.2, R114.1, U6.6 (NEG_B)
unnamed: R186.2, R188.2, R195.2, R196.2, R197.1, U15.6 (NEG_B)
unnamed: D26.A, U29.7 (OUT_B)
unnamed: D59.A, U41.7 (OUT_B)
unnamed: D33.C, R92.2, U29.5 (POS_B)
unnamed: D66.C, R153.2, U41.5 (POS_B)
unnamed: R92.1, R93.2, U31.2 (NEG_A)
unnamed: R153.1, R154.2, U43.2 (NEG_A)
unnamed: R94.1, U32.1 (OUT_A), U32.5 (POS_B)
unnamed: R155.1, U44.1 (OUT_A), U44.5 (POS_B)
unnamed: R94.2, R95.2, U32.2 (NEG_A)
unnamed: R155.2, R156.2, U44.2 (NEG_A)
unnamed: C53.2, R54.2, R55.2, R56.2
unnamed: C13.1, D35.A, D36.C, D43.A, R64.1, R76.2
unnamed: C12.1, D24.A, D25.C, D32.A, R86.1, R98.2
unnamed: C61.1, D57.A, D58.C, D65.A, R147.1, R159.2
unnamed: C21.1, U$13.11 (LHMC1)
unnamed: D29.A, D30.C, R93.1, R119.1, U32.3 (POS_A)
unnamed: C22.1, U$13.12 (LHMC4)
unnamed: R119.2, U30.5 (POS_B), U30.7 (OUT_B)
unnamed: R163.2, U42.5 (POS_B), U42.7 (OUT_B)
unnamed: C17.1, U$13.1 (LLC1)
P0A: R25.1, R28.2, U$2.5 (P0A)
P0A1: R56.1, R57.2, U$7.5 (P0A)
P0A4: R45.1, R46.2, U$3.5 (P0A)
P0A31: R139.1, R140.2, U$18.5 (P0A)
P0A_0: R19.2, U$5.5 (P0A)
P0A_1: R39.1, U$6.5 (P0A)
P0A_01: R68.2, U$11.5 (P0A)
P0A_03: R90.2, U$14.5 (P0A)
P0A_04: R151.2, U$20.5 (P0A)
P0A_11: R79.1, U$12.5 (P0A)
P0A_13: R101.1, U$15.5 (P0A)
P0A_14: R162.1, U$21.5 (P0A)
P0B: R24.1, R34.1, U$2.7 (P0B)
P0B1: R55.1, R81.1, U$7.7 (P0B)
P0B4: R44.1, R50.1, U$3.7 (P0B)
P0B31: R138.1, R164.1, U$18.7 (P0B)
P0B_1: R38.1, U10.6 (NEG_B), U$6.7 (P0B)
P0B_11: R78.1, U22.6 (NEG_B), U$12.7 (P0B)
P0B_13: R100.1, U30.6 (NEG_B), U$15.7 (P0B)
P0B_14: R161.1, U42.6 (NEG_B), U$21.7 (P0B)
P0W: R31.2, R32.1, R35.1, U$2.6 (P0W)
P0W1: R59.2, R60.1, R82.1, U$7.6 (P0W)
P0W4: R48.2, R49.1, R51.1, U$3.6 (P0W)
P0W31: R142.2, R143.1, R165.1, U$18.6 (P0W)
P0W_0: R14.1, U$5.6 (P0W)
P0W_01: R66.1, U$11.6 (P0W)
P0W_03: R88.1, U$14.6 (P0W)
P0W_04: R149.1, U$20.6 (P0W)
PA0: R17.2, U10.1 (OUT_A), U$4.8 (PA0)
PA1: R29.2, U12.6 (NEG_B), U$4.7 (PA1)
PA01: R67.2, U22.1 (OUT_A), U$10.8 (PA0)
PA03: R89.2, U30.1 (OUT_A), U$9.8 (PA0)
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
